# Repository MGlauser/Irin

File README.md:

# Irin

**The wakeful one: an always-on battery watcher for Home Assistant.**

Irin is an always-on battery monitor that clamps onto a battery's terminals and reports
**voltage, state of charge (SOC), charging activity and temperature** to
[Home Assistant](https://www.home-assistant.io/) over WiFi, with a tiny OLED readout on
the device itself.

The prototype watches the 12V accessory battery of a 2027 Subaru Uncharted GT (an EV whose
12V battery can run down in a couple of days of parking), but nothing in it is
car-specific. Change a few lines of configuration and it monitors **flooded lead-acid,
AGM, LiFePO4 or sodium-ion** batteries in **12V, 24V or 48V** systems: RVs and boats,
ham radio go-boxes and repeater power, solar and home backup banks, golf carts, stored
vehicles.

No cloud, no vehicle telematics, no OBD dongle: one ESP32 board on the battery, one
entry in your Home Assistant.

<p align="center"><sub>The included dashboard on the bench prototype. SOC steps only
after a rest window (0% from an early reboot loop, then 50%, ~17% and 42% as the bench
supply was changed); voltage is charted continuously. And 42% is, of course, the
answer.</sub></p>

### The name

*Irin* (Aramaic עִירִין, *ʿirin*; singular *ʿir*) means "watchers", literally "the
wakeful ones": those who do not sleep. It is the word for the Watchers of the Book of
Enoch, whose first part (1 Enoch 1–36) is called *The Book of the Watchers* and survives
in Aramaic among the Dead Sea Scrolls. The same word appears in Daniel 4:13: "a watcher
and a holy one came down from heaven."

The name is meant in the sense of the *holy* Watchers, the ones who kept their post
(1 Enoch 20 names them: Uriel, Raphael, Raguel, Michael, Saraqael, Gabriel and Remiel),
not the fallen ones the book is better known for.

It is also the design in one word. Deep sleep was evaluated and rejected (on the
prototype it would buy about 2% more runway), so the monitor stays awake around the
clock, watching the battery so you don't have to.

---

## What it does

| | |
|---|---|
| **Voltage** | Measured every 30 s with a 16-bit ADC (0.7 mV resolution at 12V) and published continuously, never gated. Charts charging cycles in detail. |
| **State of charge** | Looked up from *resting* voltage, temperature-corrected, and only updated when the battery has truly rested (see below). Holds its last good value otherwise, with a "last updated" timestamp. |
| **Charging** | On/off, detected from voltage with hysteresis, plus *Time Since Charging*. Shows whether the charging source (alternator, DC-DC converter, solar, shore power) is actually doing its job. |
| **Away report** | While Home Assistant is unreachable (the car is away from home WiFi, or HA is down), the device keeps a summary: lowest voltage, lowest SOC, time below the alert level, charging time and events. Published when it reconnects, e.g. *"3.2 d: SOC min 46%, 4.0 h below 50%, 6 charges"*. Gaps under 30 minutes are ignored. |
| **Temperature / humidity** | DHT22 sensor, used for the SOC temperature correction. |
| **On-device display** | Voltage, SOC, temperature and rest/charging status on a 72×40 OLED. Blanks after 2 minutes to prevent burn-in; the BOOT button wakes it. Stays lit while charging. |
| **Home Assistant** | Native ESPHome integration (no MQTT broker), a ready-made dashboard, and history for long-term battery-health trends. Alerts are ordinary HA automations. |

It draws about **10 mA at 12V** on WiFi, and about **40 mA** while out of WiFi range with
its fallback network up (see [Fallback WiFi network](#fallback-wifi-network-and-its-power-cost)).

### Why SOC needs a "rest gate"

A battery's voltage only tells you its state of charge when it has been sitting
unloaded and uncharged for a while. During and after charging it reads high (surface
charge), so a naive voltage-to-SOC lookup reports 100% on a battery that may be
failing, and a low-battery alert fires late or never.

So SOC is recomputed only after the voltage has stayed below the charging threshold for
**30 minutes** *and* has been stable (within 5 mV per 5 minutes) for **15 minutes**.
Voltage itself is never gated: you always see the raw trace.

---

## Hardware

| Part | Notes |
|---|---|
| **01Space ESP32-C3-0.42LCD** ("ESP32-C3 SuperMini 0.42 OLED") | ESP32-C3 with a built-in 72×40 SSD1306 OLED. I2C on SDA=GPIO5 / SCL=GPIO6 (verified). |
| **ADS1115** 16-bit ADC module (e.g. HiLetgo) | I2C at 0x48 (ADDR→GND), powered from 3.3V. Battery on A0 through the divider. |
| **Voltage divider** R1/R2, 1% metal film, same series | 47k / 10k for 12V systems (see the voltage table for 24/48V). |
| **C1**, 2 nF across R2 | 2× 1000 pF mica in parallel (low leakage). |
| **MP1584EN** buck module, set to 5.0V | Feeds the board's 5V pin. 12V systems only; see 24/48V below. |
| **DHT22 / AM2302** + 3-pin JST-XH (J2) | Best outside the enclosure (cable ≤1 m at 3.3V); inside works, reading a few °C warm, which errs toward an early alert. |
| **Fuse** at the battery positive terminal | 5 A, DC-rated for the system voltage. Protects the wiring, not the 10 mA load. |
| **TVS diode** D1 | P6KE18A for 12V. Fitted as standard: it clamps switching transients, and a reversed hookup forward-biases it and blows the fuse. |
| **Enclosure** | 3D printed, PETG or ASA. |

- Full bill of materials, wiring and divider math: [`PARTS.md`](PARTS.md).
- Schematic: [`hardware/`](hardware/) (KiCad 10), PDF preview in
  [`hardware/preview.pdf`](hardware/preview.pdf).
- Breadboard layout for a 400-point board: open
  [`hardware/breadboard/breadboard.html`](hardware/breadboard/breadboard.html) in a
  browser. It is generated and checked against the schematic's netlist by
  `make_breadboard.py`.

### The one wiring rule that matters

**R2 and C1 must return to the ADS1115's own GND pin, and that ground must meet power
ground at exactly one point.** If the divider and the ADC sit on different ground paths,
the supply current's voltage drop appears in series with the measurement and gets
multiplied by the divider ratio. On the prototype, 15 mV of ground drop between two
breadboard rails became an 86 mV error at the battery, and it drifted.
This applies to wired builds. On the PCB, the solid GND plane does the same job and R2/C1
connect to it directly.

---

## Build and install

### 1. Bench build
1. Set the buck module to **5.0V** before connecting it to anything.
2. Build the circuit (breadboard first is a good idea; see the layout above).
3. Power from a bench supply. Check that the OLED lights up and both I2C devices appear
   in the ESPHome log (0x3C and 0x48).

### 2. Firmware (ESPHome)
The firmware is a single ESPHome config: [`esphome/irin.yaml`](esphome/irin.yaml).

**With the Home Assistant ESPHome add-on (Device Builder):**
1. Run `python3 esphome/www/build_www.py` (needs ESPHome installed; it writes
   `esphome/irin_www.js`, the status page script), then copy the YAML and `irin_www.js`
   into `/config/esphome/`. The script isn't in the repo because it is mostly ESPHome's
   own page code.
2. Add the keys from [`esphome/secrets.yaml.example`](esphome/secrets.yaml.example) to
   the add-on's `secrets.yaml` (Secrets button in the add-on).
3. Plug the ESP32 into the HA host by USB, then **Install**. Later updates go over WiFi.

**Or with the ESPHome command line:** copy `secrets.yaml.example` to `secrets.yaml`, fill
it in, and run `esphome run irin.yaml`.

Change `device_name` and `friendly_name` at the top of the YAML for each monitor you
build; entity IDs in HA follow `friendly_name`. The files in this repository are the
prototype's own configuration, named "Uncharted 12V", so the HA examples use entity IDs
like `sensor.uncharted_12v_battery_voltage`. If your `friendly_name` is "RV House", for
example, replace `uncharted_12v` with `rv_house` throughout `ha_config/`.

### 3. Calibrate (two-point)
Every divider is different, so calibrate against a good meter:
1. In the YAML, comment out the `calibrate_linear` block and install. *Battery Voltage*
   now shows the raw voltage at A0 (about 2 V on a 12V system).
2. Set a bench supply near the **bottom** of your range (11.50 V for 12V) and measure it
   **at the board** with a DVM. Note the true voltage and the raw reading.
3. Repeat near the **top** of your charging range (15.00 V for 12V).
4. Enter both pairs as `raw -> true`, uncomment, and reinstall:
   ```yaml
   - calibrate_linear:
       - 2.00320 -> 11.500
       - 2.61497 -> 15.000
   ```
5. Verify at your SOC alert point (e.g. 12.22 V) and at the maximum (16.00 V). Expect
   ±0.01 V.

The fitted slope should land close to your measured (R1+R2)/R2. If it is off by more than
a few tenths of a percent, suspect the ground wiring (see above) before the resistors.

### 4. Home Assistant
1. Settings → Devices & services: the device appears under **Discovered**. Add it (the
   encryption key is `uncharted_api_key` from your secrets).
2. Check the entity IDs. **Gotcha:** if the device is assigned to an area, HA may prefix
   new entity IDs with it (`sensor.garage_…`). Rename them, or edit the dashboard to
   match.
3. Dashboard: create a new dashboard, open the **Raw configuration editor**, and paste
   [`ha_config/dashboard.yaml`](ha_config/dashboard.yaml). For a
   single card on an existing dashboard, use
   [`ha_config/dashboard_card.yaml`](ha_config/dashboard_card.yaml).
4. Alerts: draft automations are in [`ha_config/`](ha_config/) (low SOC, charging
   stalled, device offline). Tune thresholds against a week or two of your own data
   before relying on them.

### 5. Install on the battery
- Ring terminals directly on the battery posts, fuse within ~15 cm (6") of the positive
  terminal. No splicing into vehicle harnesses.
- **If the battery has a current sensor clamped on its negative post** (many modern
  vehicles do), connect the monitor's ground on the chassis side of the sensor, so the
  vehicle still accounts for the monitor's current.
- Temperature sensor outside the enclosure near the battery if you can; inside the box is acceptable.
- Check the WiFi signal tile in HA at the final location before closing everything up.
  Below about −80 dBm, expect dropouts.

---

## Customizing

Everything you need to change is in the `substitutions:` block at the top of
[`esphome/irin.yaml`](esphome/irin.yaml), plus the divider
resistors and calibration for other system voltages.

| Setting | What it does | 12V flooded default |
|---|---|---|
| `soc_table_v` / `soc_table_pct` | Resting voltage → SOC lookup at 25 °C, ascending, same length | flooded table below |
| `charge_on_threshold` | Above this: charging | 12.90 V |
| `charge_off_threshold` | Below this: resting (the rest gate starts counting) | 12.80 V |
| `rest_required_sec` | Time below `charge_off_threshold` before SOC updates | 1800 s |
| `stable_required_sec` | Time the voltage must also be stable | 900 s |
| `slope_tolerance` | Allowed drift per 5-minute tick to count as stable | 0.005 V |
| `temp_coeff` | Resting-voltage temperature coefficient, V/°C, for the whole battery | 0.004 |
| `display_wake_ms` | How long the OLED stays lit | 120000 |
| `ap_ssid` | Name of the fallback WiFi network (see below). Don't name the vehicle: it broadcasts wherever you park | irin-Sunny |
| `soc_alert_pct` | SOC alert level, used for the away report's "time below alert" (match your HA automation) | 50 |
| `away_min_sec` | Shortest HA outage that counts as "away" and replaces the last report | 1800 s |

**Rule for the charging thresholds:** `charge_off_threshold` must sit **above** the
battery's full resting voltage (otherwise a full, idle battery looks like it is
charging), and **below** the lowest charging voltage you expect. Put
`charge_on_threshold` about 0.1 V higher (per 12V) for hysteresis.

### Fallback WiFi network (and its power cost)

When the device can't reach its WiFi for 90 seconds, it starts its own password-protected
network (`ap_ssid`). This is how you recover after changing your WiFi password without
re-flashing:

1. Join the fallback network from a phone, using `uncharted_fallback_password` from your secrets.
2. The setup page opens (or browse to `http://192.168.4.1`). Pick your network and enter
   the new password. The device saves it and reconnects.
3. **Then update `wifi_password` in your secrets before the next firmware install.** A
   password saved this way only applies to the firmware that is running; any install with
   a changed configuration goes back to the password in the YAML.

**Status page.** The device also serves a small status page: voltage, SOC, temperature,
charging and the away report. When the device is out of WiFi range, join the fallback
network and open `http://192.168.4.1`. On your home network, use
`http://<device_name>.local` (e.g. `http://uncharted-batt.local`). Log in as `irin`, with
the fallback password. Useful when the battery is in a sealed box and the OLED is out of
reach. While the fallback network is up, the setup page is still what your phone's
network-login popup shows. If you need it in a browser, open any other address on the
device, or tap **WiFi Setup** on the status page, just above OTA Update. That link
appears only while the fallback network is up, because that is the only time the setup
page exists. It comes from `esphome/irin_www.js`, which is ESPHome's own status page
script with the link added; after upgrading ESPHome, regenerate it with
`python3 esphome/www/build_www.py` (using the ESPHome install that builds the firmware) and
copy it next to the YAML. Don't want the link? Replace `js_include` and `js_url` with
`local: true` and drop the file.

For a *planned* password change you don't need the fallback network at all: list both
passwords under `wifi: networks:` (same SSID), install over WiFi while the old one still
works, then change the router.

**The cost: about 40 mA instead of 10 mA, but only while out of WiFi range.** A device
that can't find its network keeps the radio on, searching and broadcasting. On WiFi at
home there is no extra draw. Measured on the prototype at 12V. The extra 30 mA is about
0.7 Ah a day, around 3% of the capacity between full and the 50% alert on a 50 Ah
battery: for a car parked away from home, a few hours less warning out of several days. Daily trips cost about 0.25 Ah, which the drive
home replaces.

**To turn it off**, for example on a battery bank that spends long periods out of range,
or if you'd rather not broadcast a network: delete the `ap:` block under `wifi:` and the
`captive_portal:` line, then install. The status page then only works on your home
network. To remove it as well, delete the `web_server:` block and the
`web_server: {sorting_group_id: ...}` lines. Out-of-range draw then falls to an estimated 20-30 mA
(not measured), not to 10 mA, because the radio keeps searching. The trade-offs:
- Recovering from a WiFi password change needs the planned method above, or a USB flash.
- `wifi: reboot_timeout: 60min` becomes active (ESPHome only uses it when there is no
  fallback network): the device reboots after an hour without WiFi as a recovery
  backstop. The away report survives it (kept in flash) and a full SOC rest window fits
  between reboots, but the clock comes from Home Assistant, so after such a reboot,
  charging while out of range isn't timestamped and *Time Since Charging* reads high
  until the device is back home.

### Battery chemistry (12V)

> Published voltage tables vary by manufacturer by ±0.05 V or more. If your battery's
> datasheet gives a resting-voltage curve, use it. The tables below are typical values:
> good starting points, not gospel.

#### Flooded lead-acid (default)
```yaml
soc_table_v:   "11.60, 11.75, 11.90, 12.02, 12.12, 12.22, 12.30, 12.38, 12.48, 12.58, 12.70"
soc_table_pct: "    0,    10,    20,    30,    40,    50,    60,    70,    80,    90,   100"
charge_on_threshold:  "12.90"
charge_off_threshold: "12.80"
temp_coeff: "0.004"
```
Alert at **50%**: lead-acid cycle life drops sharply below 50% depth of discharge, and a
partially discharged flooded battery sulfates. The temperature coefficient is the
battery's *open-circuit* drift (~0.7 mV/°C per cell), **not** the 3-5 mV/°C/cell charger
compensation figure. Using the charger figure over-corrects cold readings and suppresses
winter alerts.

#### AGM (and gel, as a starting point)
```yaml
soc_table_v:   "11.60, 11.80, 11.95, 12.10, 12.25, 12.35, 12.45, 12.55, 12.65, 12.75, 12.85"
soc_table_pct: "    0,    10,    20,    30,    40,    50,    60,    70,    80,    90,   100"
charge_on_threshold:  "13.10"
charge_off_threshold: "13.00"
temp_coeff: "0.004"
```
AGM rests 0.10-0.15 V higher than flooded. **Using the wrong table is the classic
mistake:** an AGM table on a flooded battery reads high and fires the 50% alert at
roughly 35-40% actual SOC. Check the battery label. Alert at 50%.

#### LiFePO4 (LFP, 4S "12.8V")
```yaml
soc_table_v:   "12.00, 12.90, 13.07, 13.13, 13.17, 13.20, 13.22, 13.25, 13.28, 13.30, 13.40"
soc_table_pct: "    0,    10,    20,    30,    40,    50,    60,    70,    80,    90,   100"
charge_on_threshold:  "13.60"
charge_off_threshold: "13.50"
temp_coeff: "0"
```
**Read this before trusting LFP SOC.** LiFePO4's resting voltage is almost flat: 20% to
90% spans only about 0.23 V, roughly 3 mV per percent, and the curve shifts with recent
charge/discharge history and temperature. Voltage-based SOC is therefore only
trustworthy near the ends of the curve (below ~20% and at full), and can be off by
10-20 points in the middle. Treat it as a **low / OK / full** indicator, and set the
alert near **20%**, where the curve bends and voltage becomes informative. LFP tolerates
deep cycling far better than lead-acid anyway. Accurate mid-range LFP SOC needs current
measurement (a shunt and coulomb counting), which this design does not do yet. The
ADS1115 has spare inputs for exactly that; see *Ideas* below.

Also: a pack's BMS may disconnect the output at low charge. If the monitor is powered
from the BMS-protected output, it goes dark exactly when the battery is lowest.

#### Sodium-ion (Na-ion, 12V packs)
Sodium-ion cells have a **sloped** discharge curve, much more like lead-acid than LFP,
so voltage-based SOC works well. Cell chemistries and pack configurations still vary
between manufacturers, so there is no universal table. Build yours from the pack's
datasheet discharge curve, or measure it (procedure below). Start with:
```yaml
temp_coeff: "0"          # until you have characterized it
charge_off_threshold:    # just above the pack's full *resting* voltage
charge_on_threshold:     # charge_off_threshold + 0.1
```
Check the pack's maximum charge voltage. The 12V divider is designed for 16 V and is
safe to about 20 V, so a pack that charges above ~15.5 V should get a slightly higher
ratio, plus recalibration.

#### Measuring your own SOC table (any chemistry)
1. Fully charge the battery, then let it rest for at least 2 hours (lead-acid: overnight).
   Record the voltage as 100%.
2. Discharge 10% of rated capacity at a gentle rate (≤ C/20) with a load and an Ah meter.
3. Rest at least 1 hour (lead-acid: 4+ hours), then record the voltage at that SOC.
4. Repeat down to your lowest acceptable level. Do this at around 25 °C.

### System voltage: 24V and 48V

The measurement chain works the same at any voltage. Four parts change in hardware,
and the per-12V numbers scale in firmware.

| | **12V** | **24V** | **48V** |
|---|---|---|---|
| Design maximum (charging + margin) | 16 V | 32 V | 64 V |
| Divider R1 / R2 | 47k / 10k | 100k / 10k | 220k / 10k |
| Ratio | 5.7 : 1 | 11 : 1 | 23 : 1 |
| A0 at design maximum | 2.80 V | 2.91 V | 2.78 V |
| Input reaches the ADS1115's 3.6 V abs. max at | 20.6 V | 39.6 V | 82.8 V |
| Resolution at the battery | 0.7 mV | 1.4 mV | 2.9 mV |
| Buck converter input rating | MP1584EN (28 V max) OK | **≥ 60 V** (24V lead-acid charges to ~29 V; the MP1584 is **not** OK) | **≥ 100 V** |
| TVS | P6KE18A | P6KE36A (30.8 V standoff: skip it if you equalize above ~30.5 V) | SMBJ60A (60 V standoff): LFP 16S and lead-acid without equalization |
| Fuse | 32 V DC automotive blade OK | 32 V DC blade OK | **58 V DC-rated** blade fuse; standard automotive blades are only 32 V |
| Calibration points | 11.5 V / 15.0 V | 23 V / 30 V | 46 V / 60 V |

Choosing parts for other cases:
- **Divider:** keep A0 at or below ~2.9 V at your design maximum, so the ADS1115 (powered
  at 3.3V) has margin to its 3.6 V absolute maximum. Keep R2 around 10k so the source
  impedance stays low.
- **TVS:** its standoff voltage must be at or above your maximum charging voltage, and its
  clamping voltage must be below the buck's maximum input.
- **Buck:** check the converter chip's datasheet input rating, not the seller's headline
  number.

**Firmware for 24V / 48V:** multiply every per-battery voltage by 2 (24V) or 4 (48V):
`soc_table_v`, both charging thresholds, `slope_tolerance` and `temp_coeff`. Lead-acid
and LFP tables scale exactly with cell count (a 12V lead-acid battery is 6 cells, 24V
is 12, 48V is 24; 12V LFP is 4S, 24V is 8S, 48V is 16S). Then calibrate as above. The
display and HA entities need no changes.

---

## Things that will bite you

- **SOC is only valid at rest.** Do not shorten the rest gate to get more frequent
  updates; surface charge reads high, which inflates SOC and fires the low alert late.
  SOC is often hours old. That's what the *SOC Last Updated* timestamp is for.
- **Match the SOC table to the chemistry** (see above).
- **Analog ground** (see *The one wiring rule that matters*).
- **The ADS1115 must be powered from 3.3V, not 5V.** The divider ratio protects a 3.3V
  part; at 5V the input ceiling and the math both change.
- **Mislabeled resistors exist.** Measure R1 and R2 before soldering. The prototype got a
  "100k" from a resistor strip that measured 100 Ω.
- **WiFi is required.** ESPHome needs it. The device keeps measuring and updating its
  display without HA (and won't reboot just because HA is down), but nothing reaches
  your phone; the away report fills in the summary on reconnect, but not the minute-by-
  minute history, and can't alert you while away. Remote sites without WiFi would need a
  different radio (LoRa, Meshtastic, cellular).

## Ideas / roadmap

- Current shunt on the ADS1115's spare A2/A3 inputs (differential mode), or an INA226,
  for coulomb counting: accurate LFP SOC, real Ah in and out.
- Second divider on A1 for dual-bank systems (an RV's starter and house batteries).
- ESPHome *packages*: a shared base config plus a short per-install file with just
  chemistry and voltage settings.
- A small PCB, possibly as a club kit.

## Repository layout

| Path | Contents | License |
|---|---|---|
| `esphome/` | ESPHome firmware config, secrets template, status page script (`www/` builds it) | MIT |
| `ha_config/` | HA dashboard, draft automations, config snippets | MIT |
| `hardware/` | KiCad schematic, PCB placement, custom footprints, netlist, PDF preview | CERN-OHL-P-2.0 |
| `hardware/breadboard/` | Breadboard layout generator (Python) and its HTML output | MIT |
| `docs/images/` | Screenshots | MIT |
| `PARTS.md` | Bill of materials, wiring, divider math | MIT |
| `CLAUDE.md` | Full design record: rationale, measurements, rejected options, bench log. Written as context for the AI assistant used to develop the project, and the most detailed technical reference here. | MIT |

## Status

Bench-verified (October 2026): calibration within ±0.01 V from 11.5 to 16 V, the rest
gate and temperature correction, the charging-detection hysteresis, the display timeout,
and Home Assistant integration. Next: perfboard build, enclosure, in-vehicle data, then
tuned alerts.

## Versioning

The firmware carries a version, `irin_version` at the top of
[`esphome/irin.yaml`](esphome/irin.yaml) (currently **0.3.0**). It shows in two places:

- **Home Assistant device page** (Settings → Devices → your device): the firmware line
  shows the ESPHome version and `mglauser.irin` plus the Irin version.
- **Firmware** sensor, in the Diagnostics group of the status page and in HA, e.g.
  *"Irin 0.3.0, ESPHome 2026.9.1, built 2026-10-07 13:20:00 -0700"*. The build time
  changes on every install, so you can always tell whether an install took effect, even
  if nobody bumped the version.

**When reporting a problem, include the Firmware line.**

Rules for changes (semantic versioning, `MAJOR.MINOR.PATCH`):

| Change | Bump | Example |
|---|---|---|
| Fix that doesn't change what the device reports | PATCH | 0.3.0 → 0.3.1 |
| New feature or entity, changed behavior or default tunable | MINOR | 0.3.1 → 0.4.0 |
| Change that breaks existing installs (renamed entities, new required secret, new wiring) | MAJOR (MINOR while 0.x) | |

- Bump `irin_version` **in the same commit** as the YAML change, add a line under
  [Changelog](#changelog), and tag the commit: `git tag v0.3.1 && git push --tags`.
- Docs-only, dashboard-only, and hardware-file changes don't bump the firmware version.
- Still 0.x: a prototype that is still changing. **1.0.0** is planned for when the
  reference build is installed on the battery in its enclosure and the alerts are proven.

### Changelog

- **0.3.0** (2026-10-07). First versioned build. Away report, fallback network
  `irin-<car>` with a WiFi Setup link on the status page, readable uptime, rest gate
  requires a true 30 minutes of observed rest, Firmware sensor.

## License

- **Software** (firmware, HA configs, scripts, documentation): [MIT](LICENSE)
- **Hardware design files** in `hardware/` (except `hardware/breadboard/`):
  [CERN Open Hardware Licence v2, Permissive (CERN-OHL-P-2.0)](hardware/LICENSE)

Provided as-is. You are working on battery systems that can deliver very large currents.
Fuse at the battery, insulate everything, and know your vehicle's service precautions.

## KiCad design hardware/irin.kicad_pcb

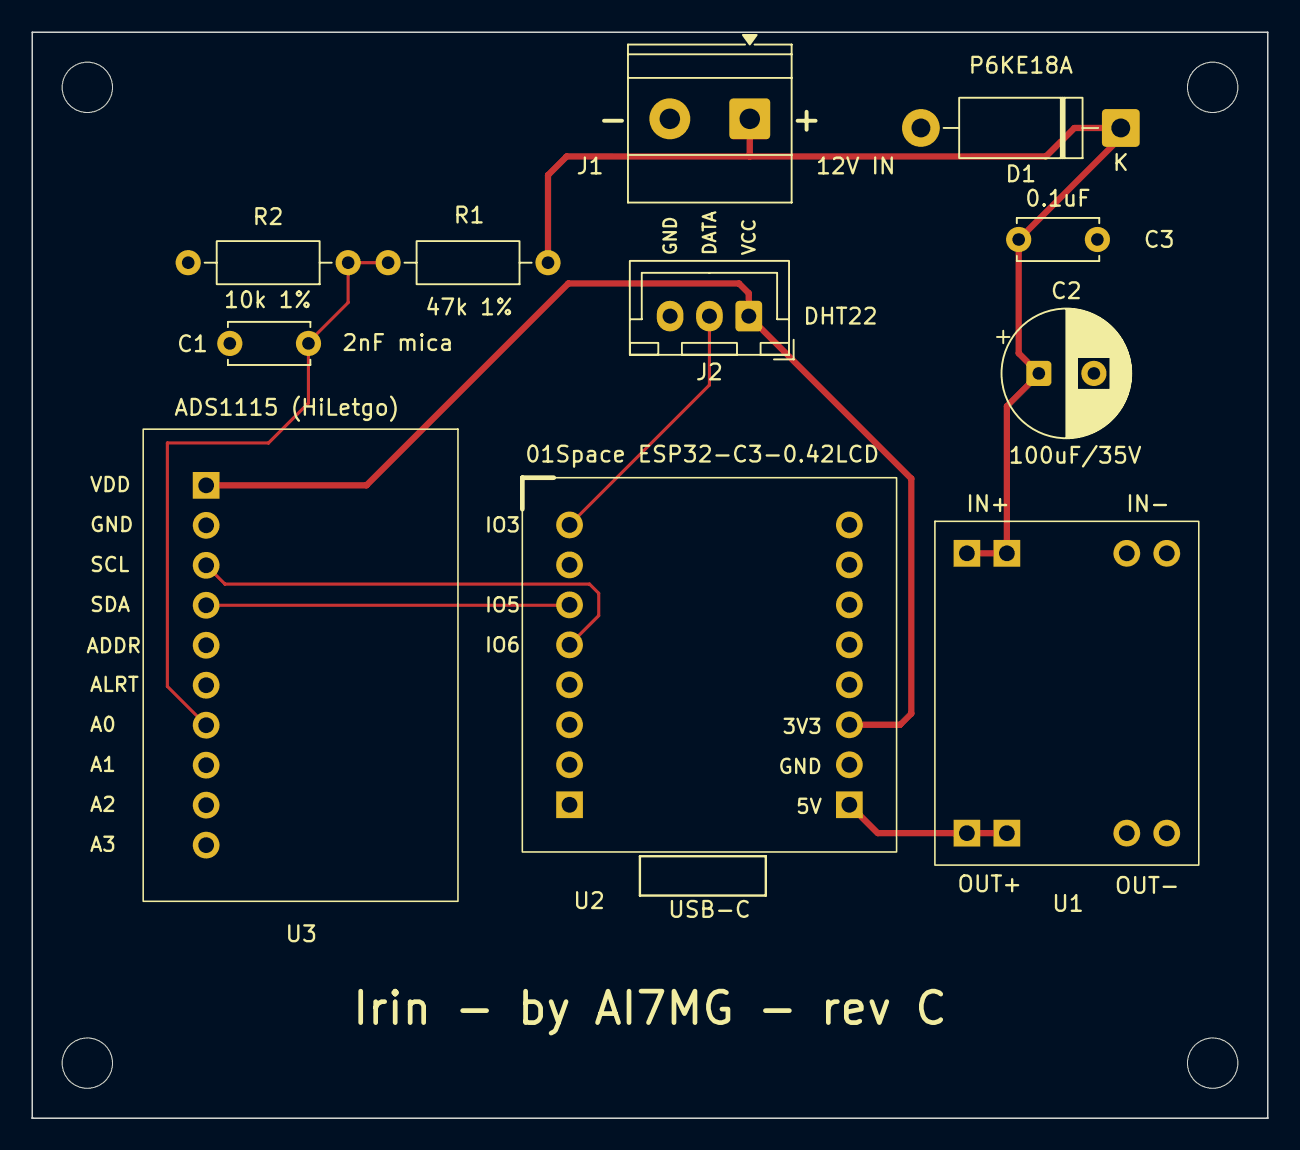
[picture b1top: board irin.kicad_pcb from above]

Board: 2 copper layers, 78.5 x 69.0 mm, 15 parts (0 on the bottom side), 8 nets.

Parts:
C1: 2nF mica; C_Disc_D5.0mm_W2.5mm_P5.00mm
C2: 100uF/35V; CP_Radial_D8.0mm_P3.50mm
C3: 0.1uF; C_Disc_D5.0mm_W2.5mm_P5.00mm
D1: P6KE18A; D_DO-15_P12.70mm_Horizontal
H1, H2, H3, H4: MountingHole_3.2mm_M3
J1: 12V IN; TerminalBlock_Phoenix_MKDS-1,5-2-5.08_1x02_P5.08mm_Horizont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
J2: DHT22; JST_XH_B3B-XH-A_1x03_P2.50mm_Vertical
R1: 47k 1%; R_Axial_DIN0207_L6.3mm_D2.5mm_P10.16mm_Horizontal
R2: 10k 1%; R_Axial_DIN0207_L6.3mm_D2.5mm_P10.16mm_Horizontal
U1: MP1584EN set to 5.0V; MP1584EN_HW133_2x2Pad_P2.54mm_W10.16mm_L17.78mm
U2: 01Space ESP32-C3-0.42LCD; ESP32C3_042LCD_2x8_P2.54mm_W17.78mm
U3: ADS1115 (HiLetgo); ADS1115_HiLetgo_1x10_P2.54mm_W18mm_L28.3mm

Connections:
/12vPROT: C2.1 (+), C3.1, D1.1 (K), J1.1 (BATT+), R1.1, U1.1 (IN+)
/GND: C1.2, C2.2 (-), C3.2, D1.2 (A), J1.2 (GND), J2.3 (GND), R2.2, U1.2 (IN-), U1.4 (OUT-), U2.3 (GND), U3.2 (GND), U3.5 (ADDR)
unnamed: J2.2 (DATA), U2.4 (GPIO3)
unnamed: J2.1 (VCC), U2.2 (3V3), U3.1 (VDD)
unnamed: U1.3 (OUT+), U2.1 (5V)
unnamed: U2.5 (GPIO5), U3.4 (SDA)
unnamed: U2.6 (GPIO6), U3.3 (SCL)
unnamed: C1.1, R1.2, R2.1, U3.6 (A0)
